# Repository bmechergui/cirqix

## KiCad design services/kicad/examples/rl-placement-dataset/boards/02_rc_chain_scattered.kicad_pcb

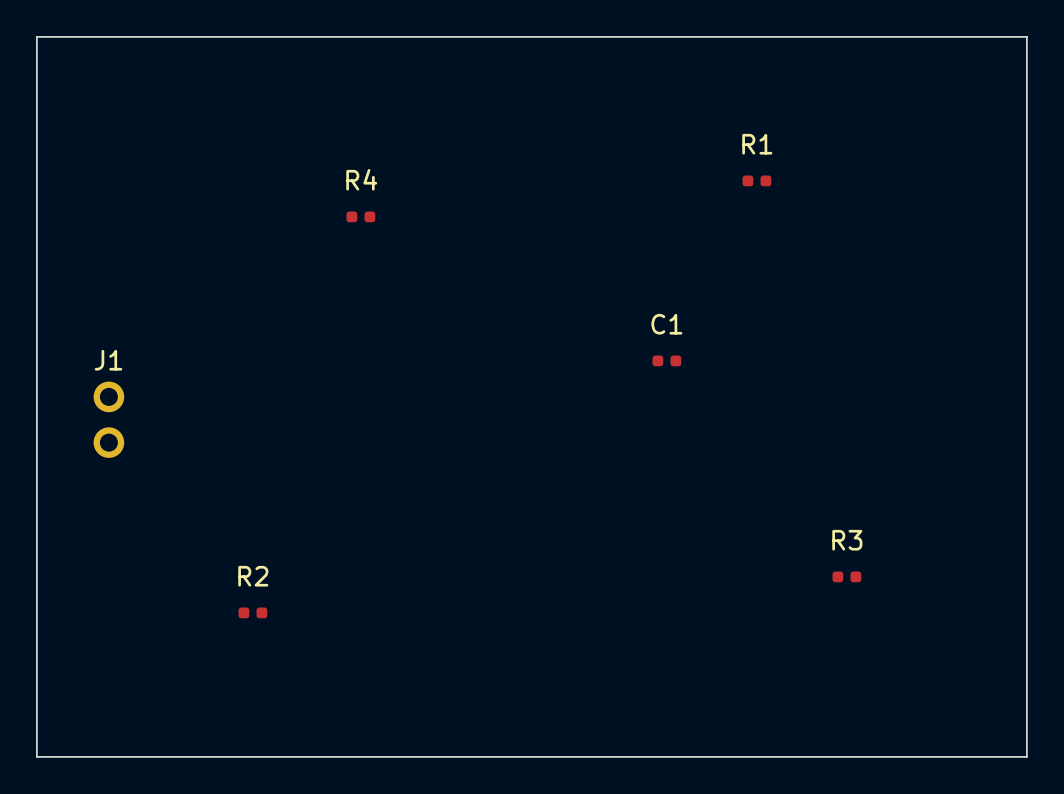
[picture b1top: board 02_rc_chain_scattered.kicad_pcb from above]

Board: 2 copper layers, 55.0 x 40.0 mm, 6 parts (0 on the bottom side), 5 nets, no tracks yet.

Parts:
C1: 100n; C_0402_1005Metric
J1: Conn; PinHeader_1x02_P2.54mm_Vertical
R1, R2, R3, R4: 10k; R_0402_1005Metric

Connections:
GND: C1.2, J1.2, R4.2
N1: R1.2, R2.1
N2: R2.2, R3.1
N3: C1.1, R3.2, R4.1
VIN: J1.1, R1.1

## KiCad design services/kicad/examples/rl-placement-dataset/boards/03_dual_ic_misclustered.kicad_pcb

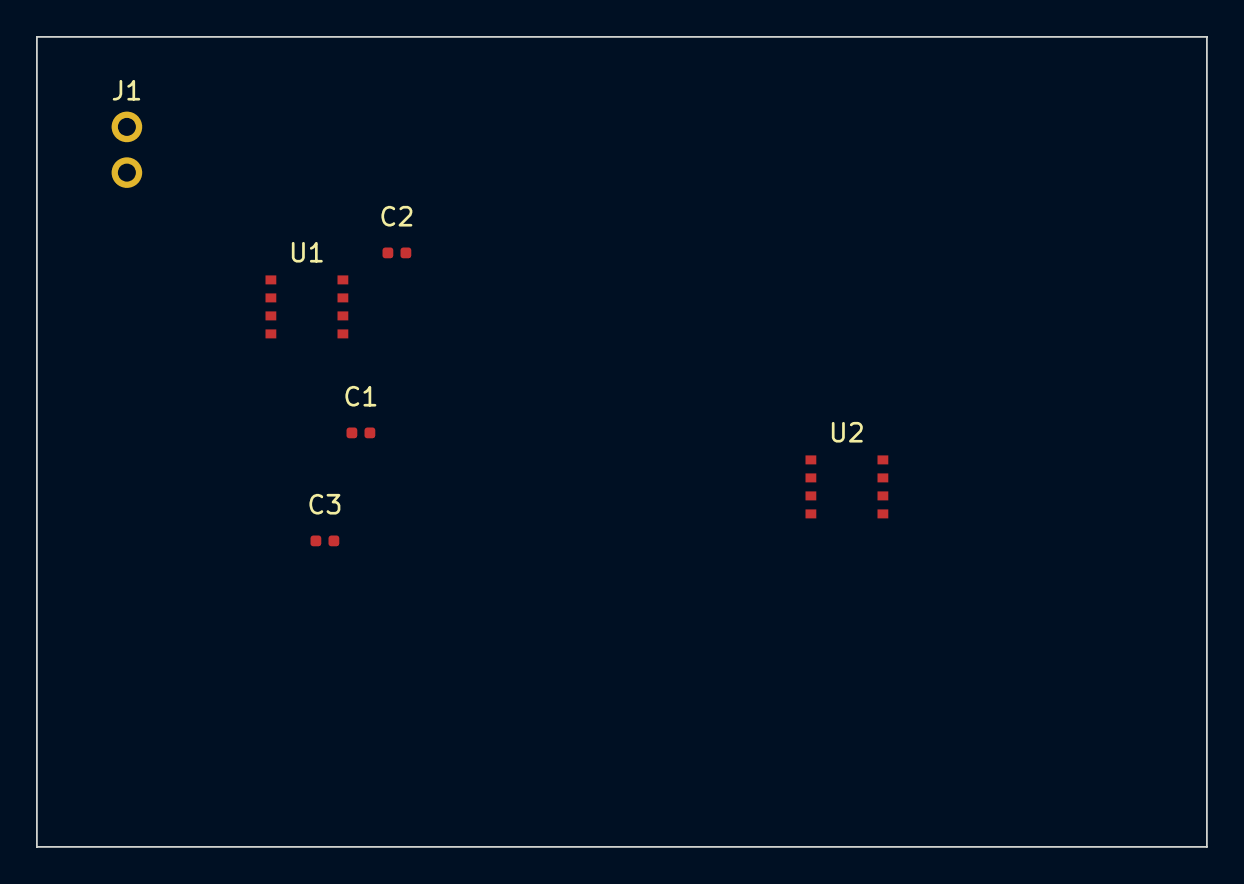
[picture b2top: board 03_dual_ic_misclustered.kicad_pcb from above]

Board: 2 copper layers, 65.0 x 45.0 mm, 6 parts (0 on the bottom side), 2 nets, no tracks yet.

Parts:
C1, C2, C3: 100n; C_0402_1005Metric
J1: Conn; PinHeader_1x02_P2.54mm_Vertical
U1, U2: IC; SOIC-8_3.9x4.9mm_P1.27mm

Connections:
GND: C1.2, C2.2, C3.2, J1.2, U1.4, U1.5, U2.4, U2.5
VCC: C1.1, C2.1, C3.1, J1.1, U1.1, U1.8, U2.1, U2.8

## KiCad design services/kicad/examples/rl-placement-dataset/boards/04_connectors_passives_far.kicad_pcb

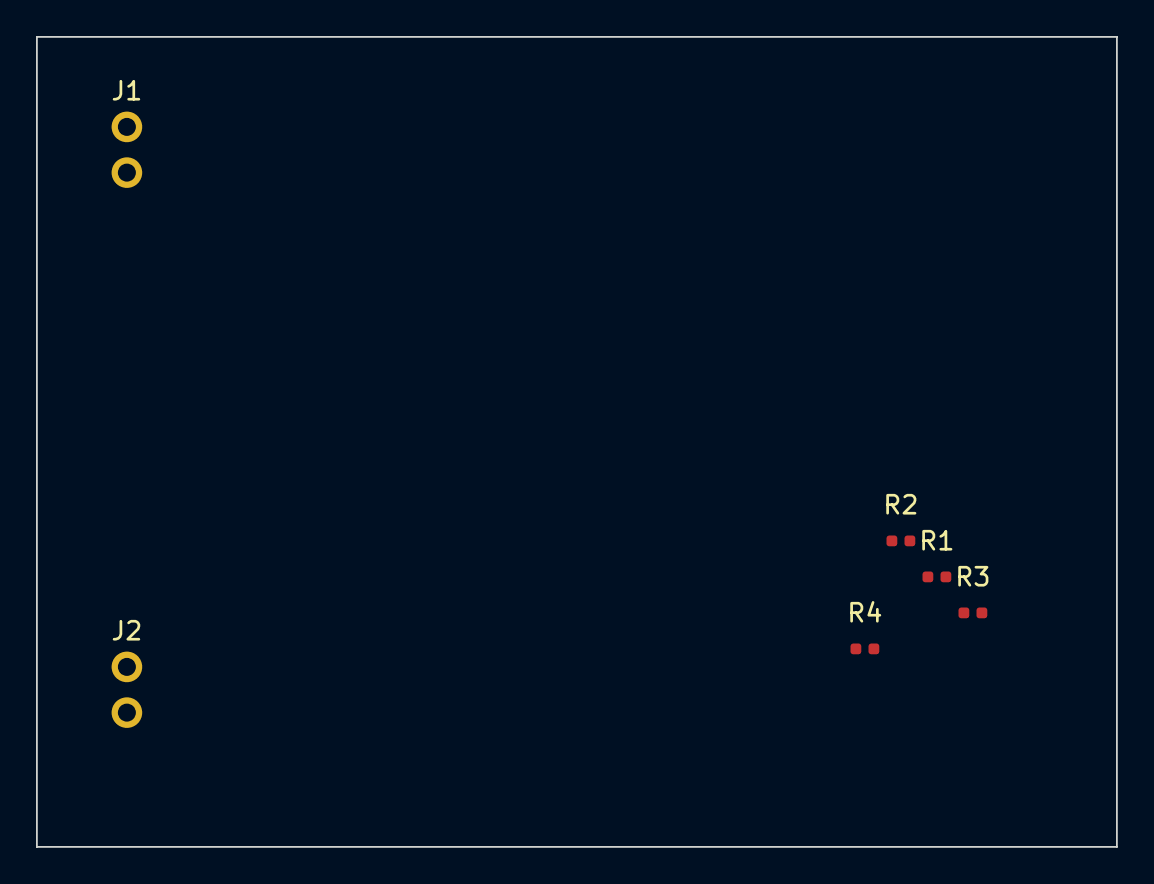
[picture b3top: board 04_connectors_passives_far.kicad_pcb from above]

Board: 2 copper layers, 60.0 x 45.0 mm, 6 parts (0 on the bottom side), 3 nets, no tracks yet.

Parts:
J1, J2: Conn; PinHeader_1x02_P2.54mm_Vertical
R1, R2, R3, R4: 10k; R_0402_1005Metric

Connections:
GND: J1.2, J2.2, R1.2, R2.2, R3.2, R4.2
SIG: J2.1, R3.1, R4.1
VCC: J1.1, R1.1, R2.1

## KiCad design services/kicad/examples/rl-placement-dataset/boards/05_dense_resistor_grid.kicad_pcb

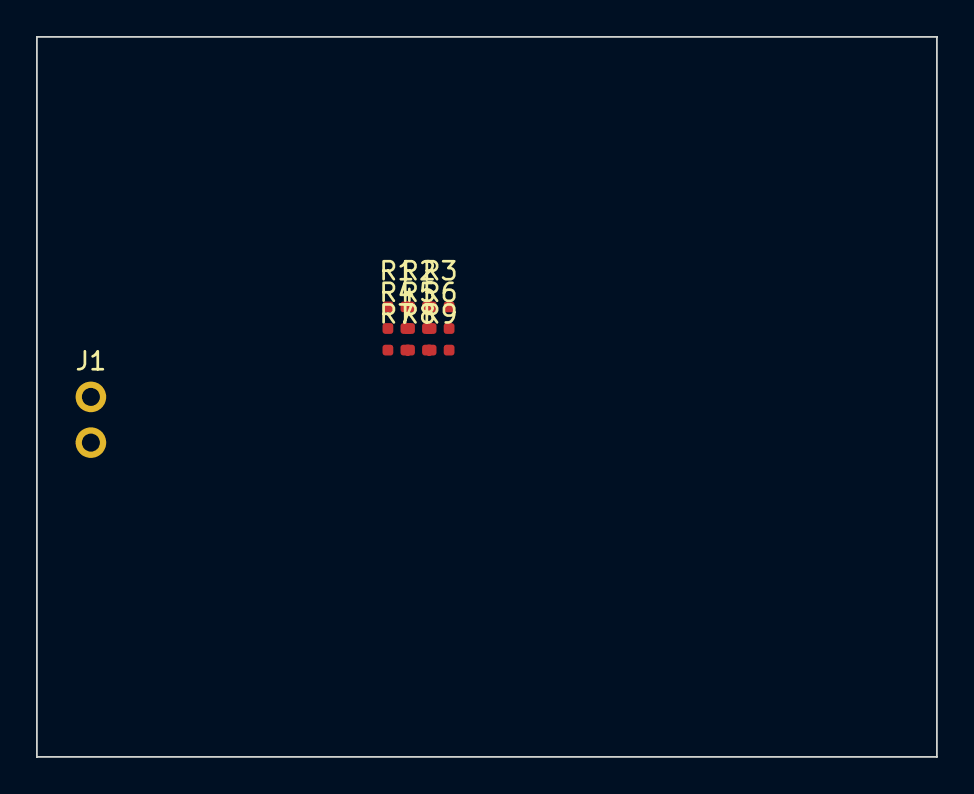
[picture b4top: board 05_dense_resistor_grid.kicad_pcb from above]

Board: 2 copper layers, 50.0 x 40.0 mm, 10 parts (0 on the bottom side), 9 nets, no tracks yet.

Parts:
J1: Conn; PinHeader_1x02_P2.54mm_Vertical
R1, R2, R3, R4, R5, R6, R7, R8, R9: 10k; R_0402_1005Metric

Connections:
GND: J1.2, R9.2
N2: R1.2, R2.1
N3: R2.2, R3.1
N4: R3.2, R4.1
N5: R4.2, R5.1
N6: R5.2, R6.1
N7: R6.2, R7.1
N8: R7.2, R8.1
N9: R8.2, R9.1

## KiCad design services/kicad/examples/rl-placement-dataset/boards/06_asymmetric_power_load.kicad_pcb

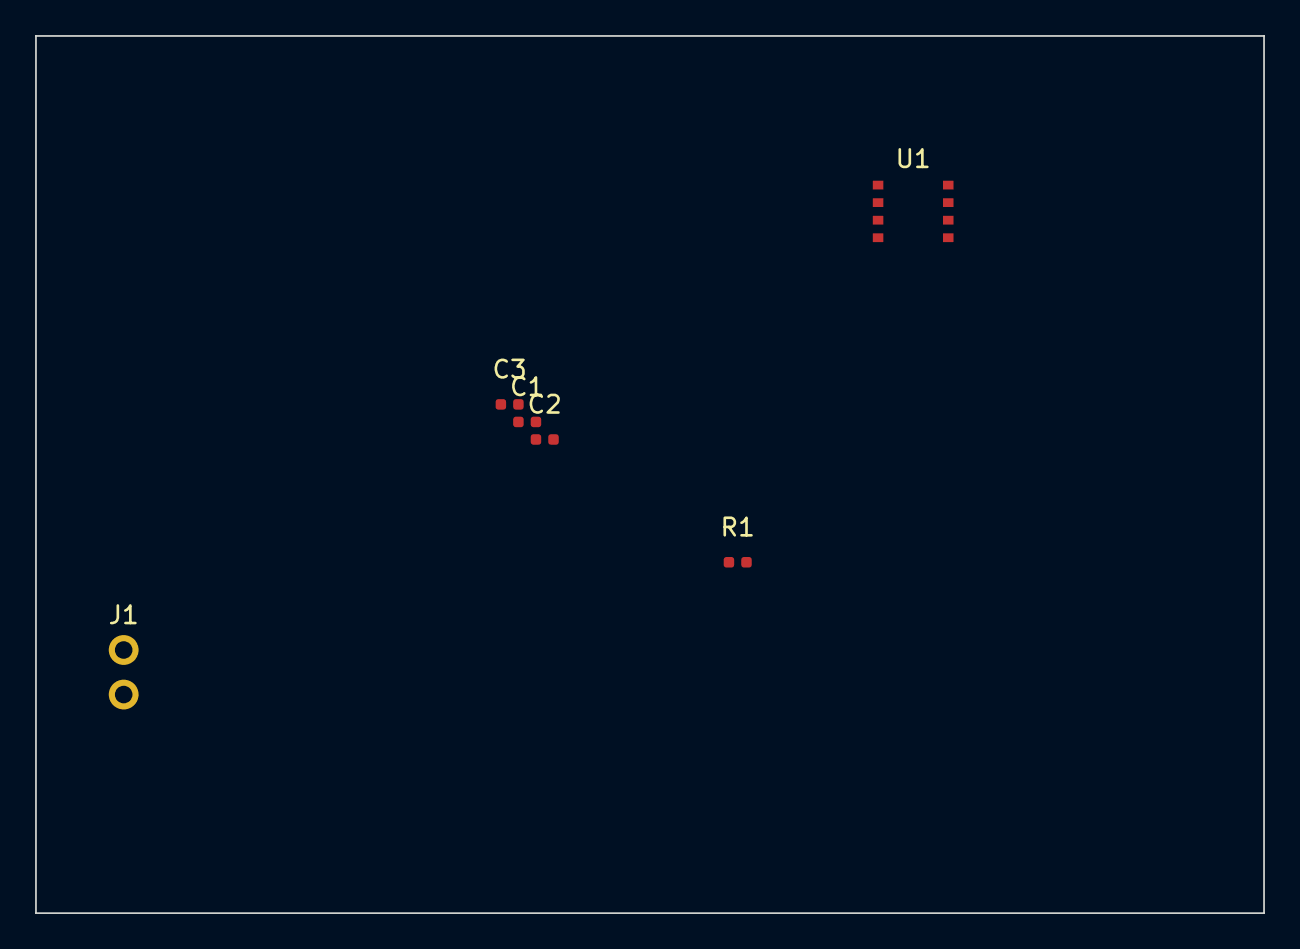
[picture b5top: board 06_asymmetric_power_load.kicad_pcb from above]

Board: 2 copper layers, 70.0 x 50.0 mm, 6 parts (0 on the bottom side), 3 nets, no tracks yet.

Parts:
C1, C2, C3: 100n; C_0402_1005Metric
J1: Conn; PinHeader_1x02_P2.54mm_Vertical
R1: 10k; R_0402_1005Metric
U1: IC; SOIC-8_3.9x4.9mm_P1.27mm

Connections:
GND: C1.2, C2.2, C3.2, J1.2, U1.4, U1.5
IO1: R1.2, U1.2
VCC: C1.1, C2.1, C3.1, J1.1, R1.1, U1.1, U1.8

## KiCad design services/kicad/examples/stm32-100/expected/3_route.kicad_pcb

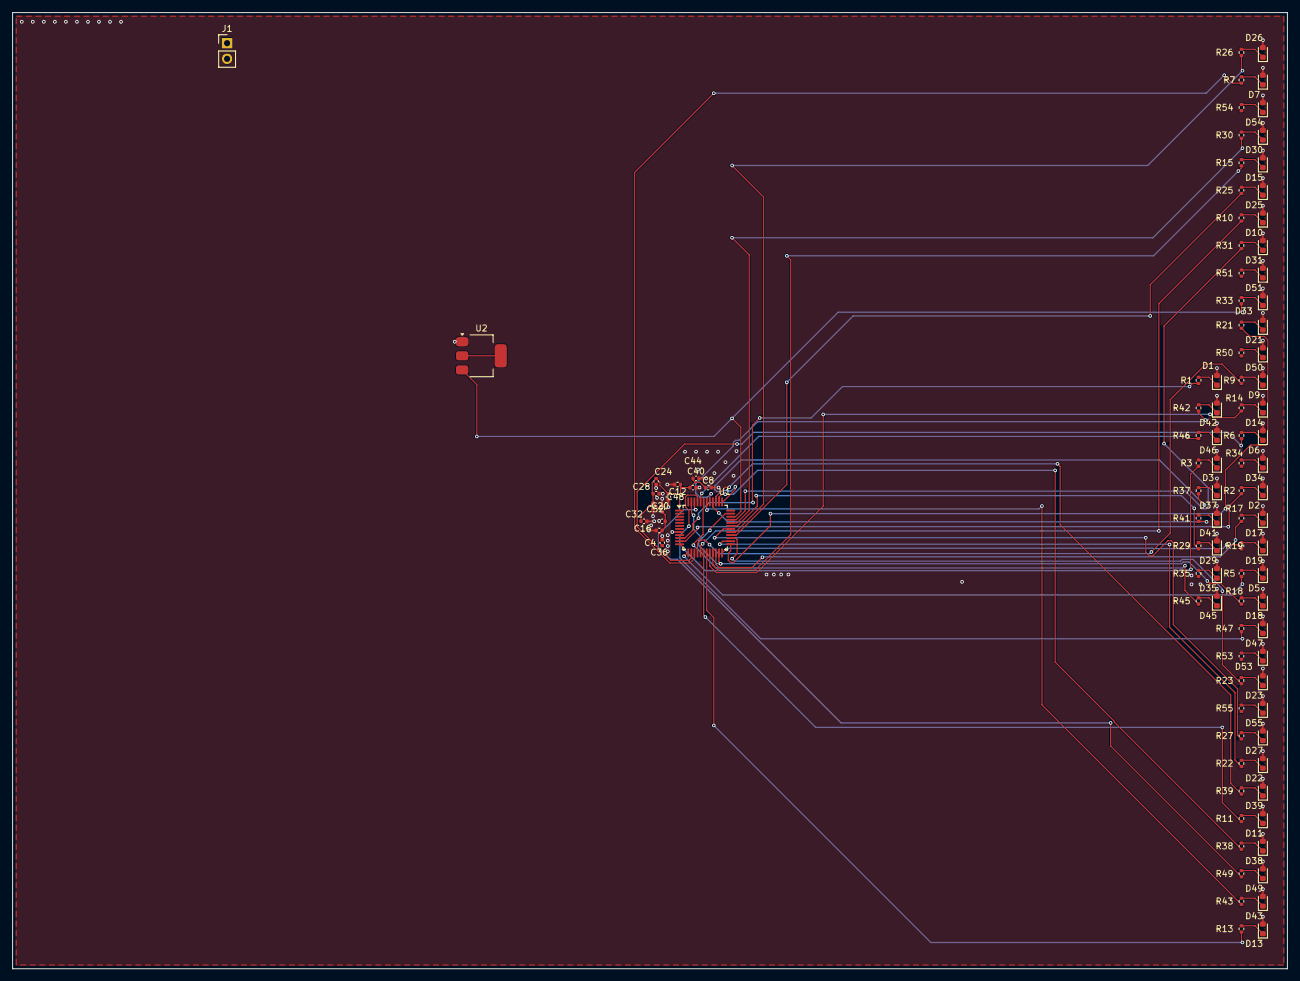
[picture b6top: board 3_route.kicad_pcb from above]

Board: 2 copper layers, 208.0 x 156.0 mm, 100 parts (0 on the bottom side), 79 nets.

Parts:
C4, C8, C12, C16, C20, C24, C28, C32, C36, C40, C44, C48, C52: 100nF; C_0402_1005Metric
D1, D2, D3, D5, D6, D7, D9, D10, D11, D13, D14, D15, D17, D18, D19, D21, D22, D23, D25, D26, D27, D29, D30, D31, D33, D34, D35, D37, D38, D39, D41, D42, D43, D45, D46, D47, D49, D50, D51, D53, D54, D55: LED; LED_0603_1608Metric
J1: 5V; PinHeader_1x02_P2.54mm_Vertical
R1, R2, R3, R5, R6, R7, R9, R10, R11, R13, R14, R15, R17, R18, R19, R21, R22, R23, R25, R26, R27, R29, R30, R31, R33, R34, R35, R37, R38, R39, R41, R42, R43, R45, R46, R47, R49, R50, R51, R53, R54, R55: 330; R_0402_1005Metric
U1: STM32F103C8T6; LQFP-48_7x7mm_P0.5mm
U2: AMS1117-3.3; SOT-223-3_TabPin2

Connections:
+3V3: C4.1, C8.1, C12.1, C16.1, C20.1, C24.1, C28.1, C32.1, C36.1, C40.1, C44.1, C48.1, C52.1, U1.1
GND: C4.2, C8.2, C12.2, C16.2, C20.2, C24.2, C28.2, C32.2, C36.2, C40.2, C44.2, C48.2, C52.2, D1.2, D2.2, D3.2, D5.2, D6.2, D7.2, D9.2, D10.2, D11.2, D13.2, D14.2, D15.2, D17.2, D18.2, D19.2, D21.2, D22.2, D23.2, D25.2, D26.2, D27.2, D29.2, D30.2, D31.2, D33.2, D34.2, D35.2, D37.2, D38.2, D39.2, D41.2, D42.2, D43.2, D45.2, D46.2, D47.2, D49.2, D50.2, D51.2, D53.2, D54.2, D55.2, J1.2, U1.8, U2.1
GPIO1: R1.1, U1.10
GPIO2: R2.1, U1.11
GPIO3: R3.1, U1.12
GPIO5: R5.1, U1.13
GPIO6: R6.1, U1.14
GPIO7: R7.1, U1.15
GPIO9: R9.1, U1.16
GPIO10: R10.1, U1.17
GPIO11: R11.1, U1.18
GPIO13: R13.1, U1.19
GPIO14: R14.1, U1.20
GPIO15: R15.1, U1.21
GPIO17: R17.1, U1.22
GPIO18: R18.1, U1.23, U1.35, U1.47
GPIO19: R19.1, U1.24
GPIO21: R21.1, U1.25
GPIO22: R22.1, U1.26
GPIO23: R23.1, U1.27
GPIO25: R25.1, U1.28
GPIO26: R26.1, U1.29
GPIO27: R27.1, U1.30
GPIO29: R29.1, U1.31
GPIO30: R30.1, U1.32
GPIO31: R31.1, U1.33
GPIO33: R33.1, U1.34, U2.3
GPIO37: R37.1, U1.37
GPIO38: R38.1, U1.38
GPIO39: R39.1, U1.39
GPIO41: R41.1, U1.40
GPIO42: R42.1, U1.41
GPIO43: R43.1, U1.42
GPIO45: R45.1, U1.43
GPIO46: R46.1, U1.44
GPIO47: R47.1, U1.45
GPIO49: R49.1, U1.46
LED1: D1.1, R1.2
LED2: D2.1, R2.2
LED3: D3.1, R3.2
LED5: D5.1, R5.2
LED6: D6.1, R6.2
LED7: D7.1, R7.2
LED9: D9.1, R9.2
LED10: D10.1, R10.2
LED11: D11.1, R11.2
LED13: D13.1, R13.2
LED14: D14.1, R14.2
LED15: D15.1, R15.2
LED17: D17.1, R17.2
LED18: D18.1, R18.2
LED19: D19.1, R19.2
LED21: D21.1, R21.2
LED22: D22.1, R22.2
LED23: D23.1, R23.2
LED25: D25.1, R25.2
LED26: D26.1, R26.2
LED27: D27.1, R27.2
LED29: D29.1, R29.2
LED30: D30.1, R30.2
LED31: D31.1, R31.2
LED33: D33.1, R33.2
LED34: D34.1, R34.2
LED35: D35.1, R35.2
LED37: D37.1, R37.2
LED38: D38.1, R38.2
LED39: D39.1, R39.2
LED41: D41.1, R41.2
LED42: D42.1, R42.2
LED43: D43.1, R43.2
LED45: D45.1, R45.2
LED46: D46.1, R46.2
LED47: D47.1, R47.2
LED49: D49.1, R49.2
LED50: D50.1, R50.2
LED51: D51.1, R51.2
LED53: D53.1, R53.2
LED54: D54.1, R54.2
LED55: D55.1, R55.2
